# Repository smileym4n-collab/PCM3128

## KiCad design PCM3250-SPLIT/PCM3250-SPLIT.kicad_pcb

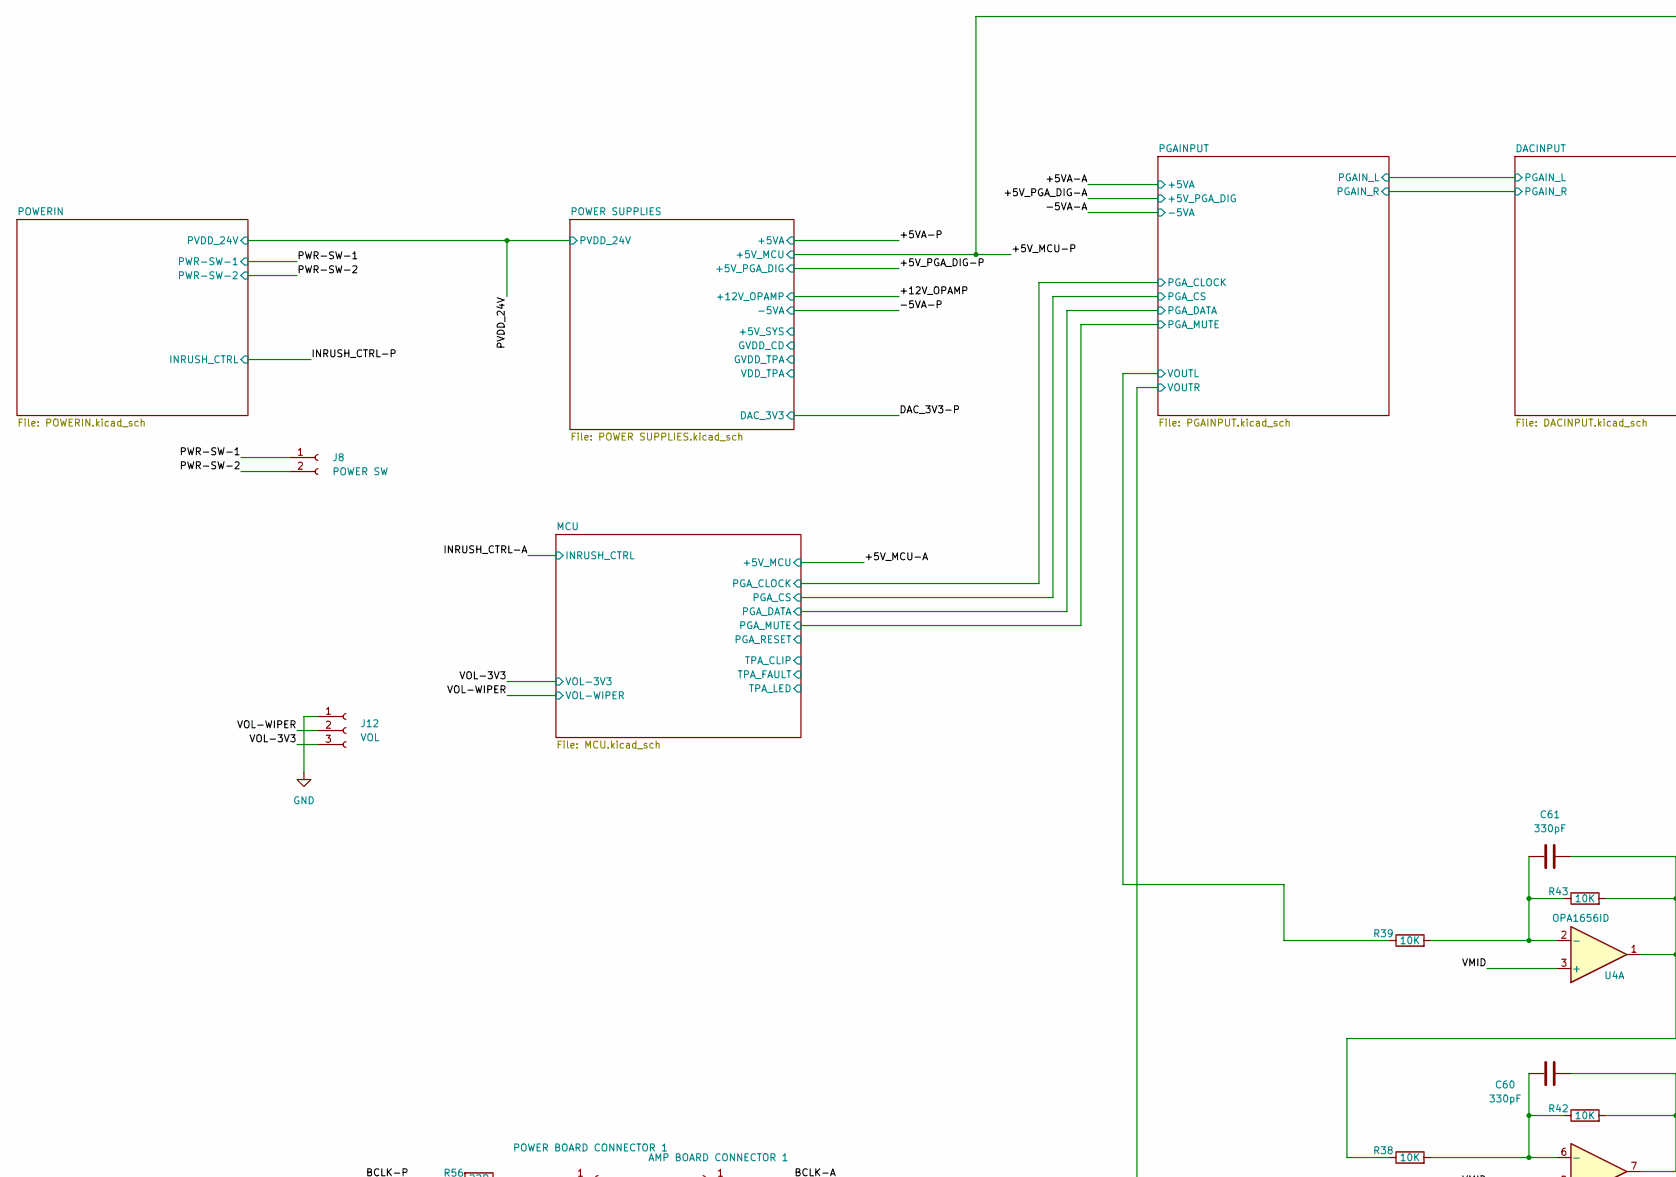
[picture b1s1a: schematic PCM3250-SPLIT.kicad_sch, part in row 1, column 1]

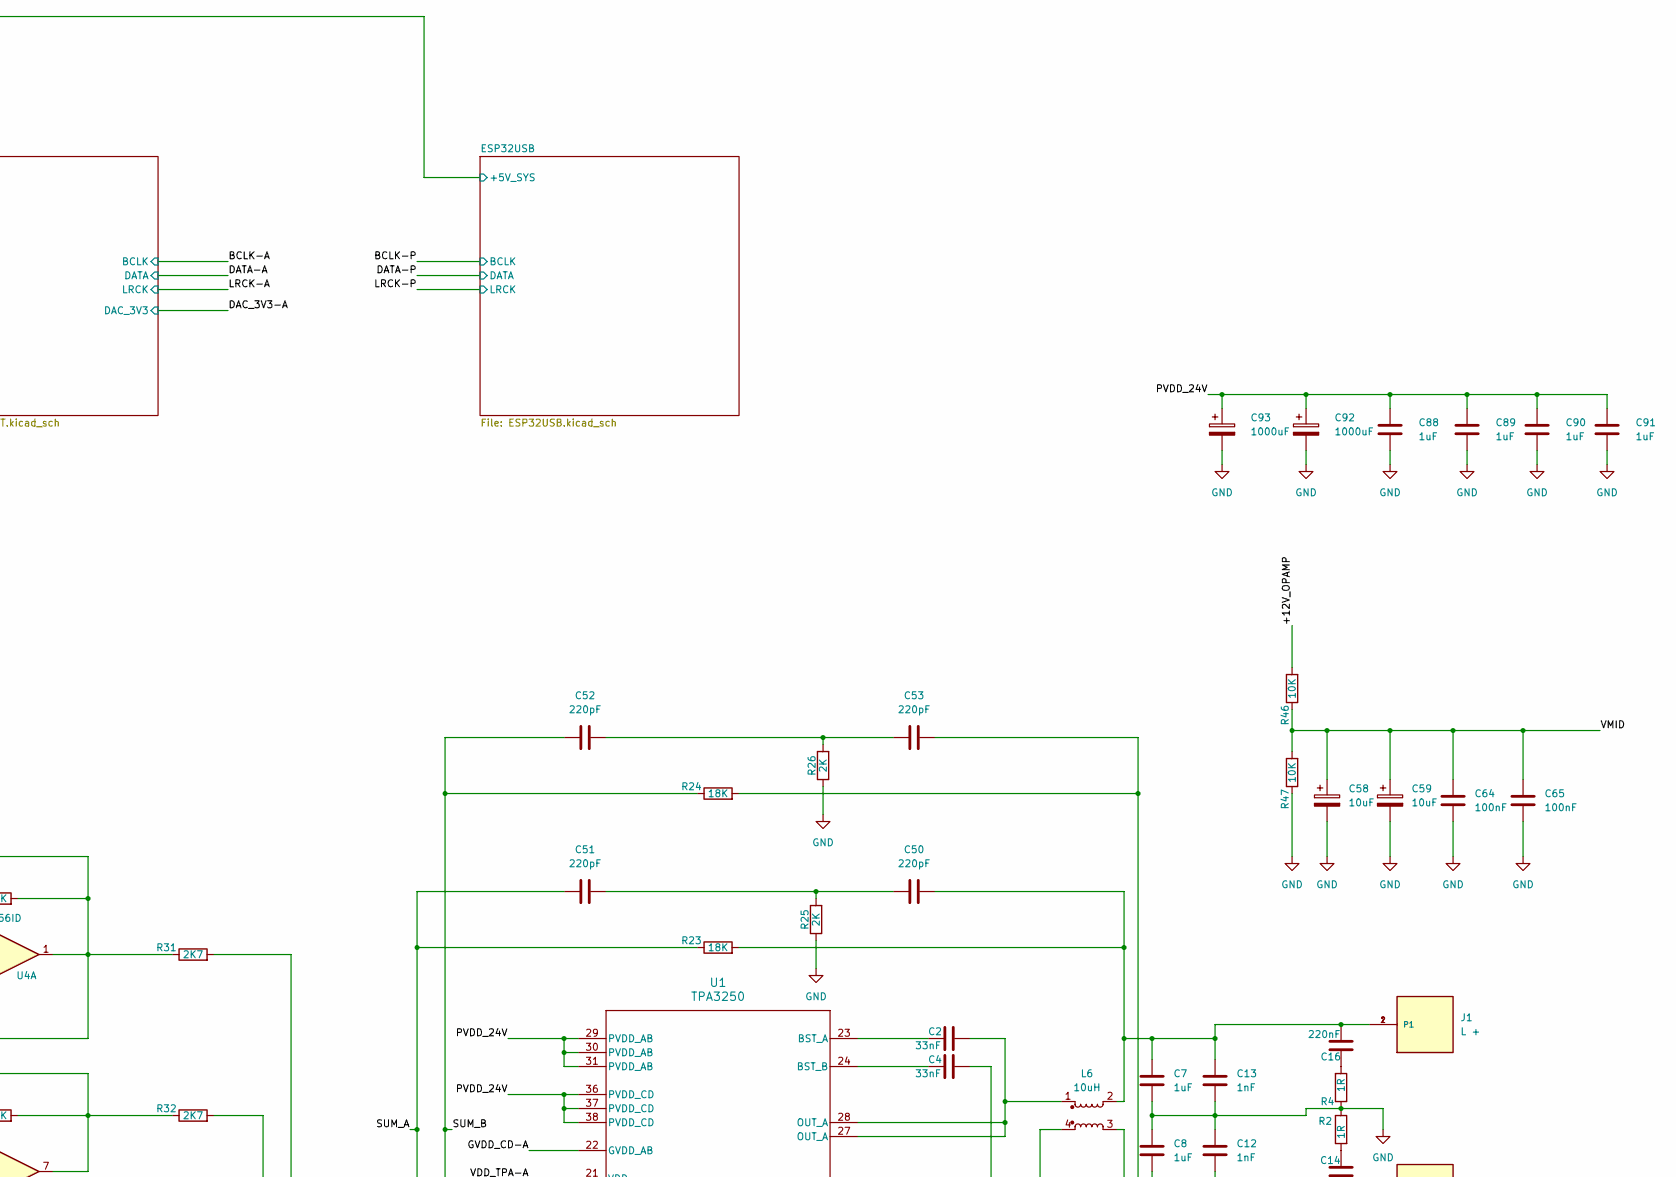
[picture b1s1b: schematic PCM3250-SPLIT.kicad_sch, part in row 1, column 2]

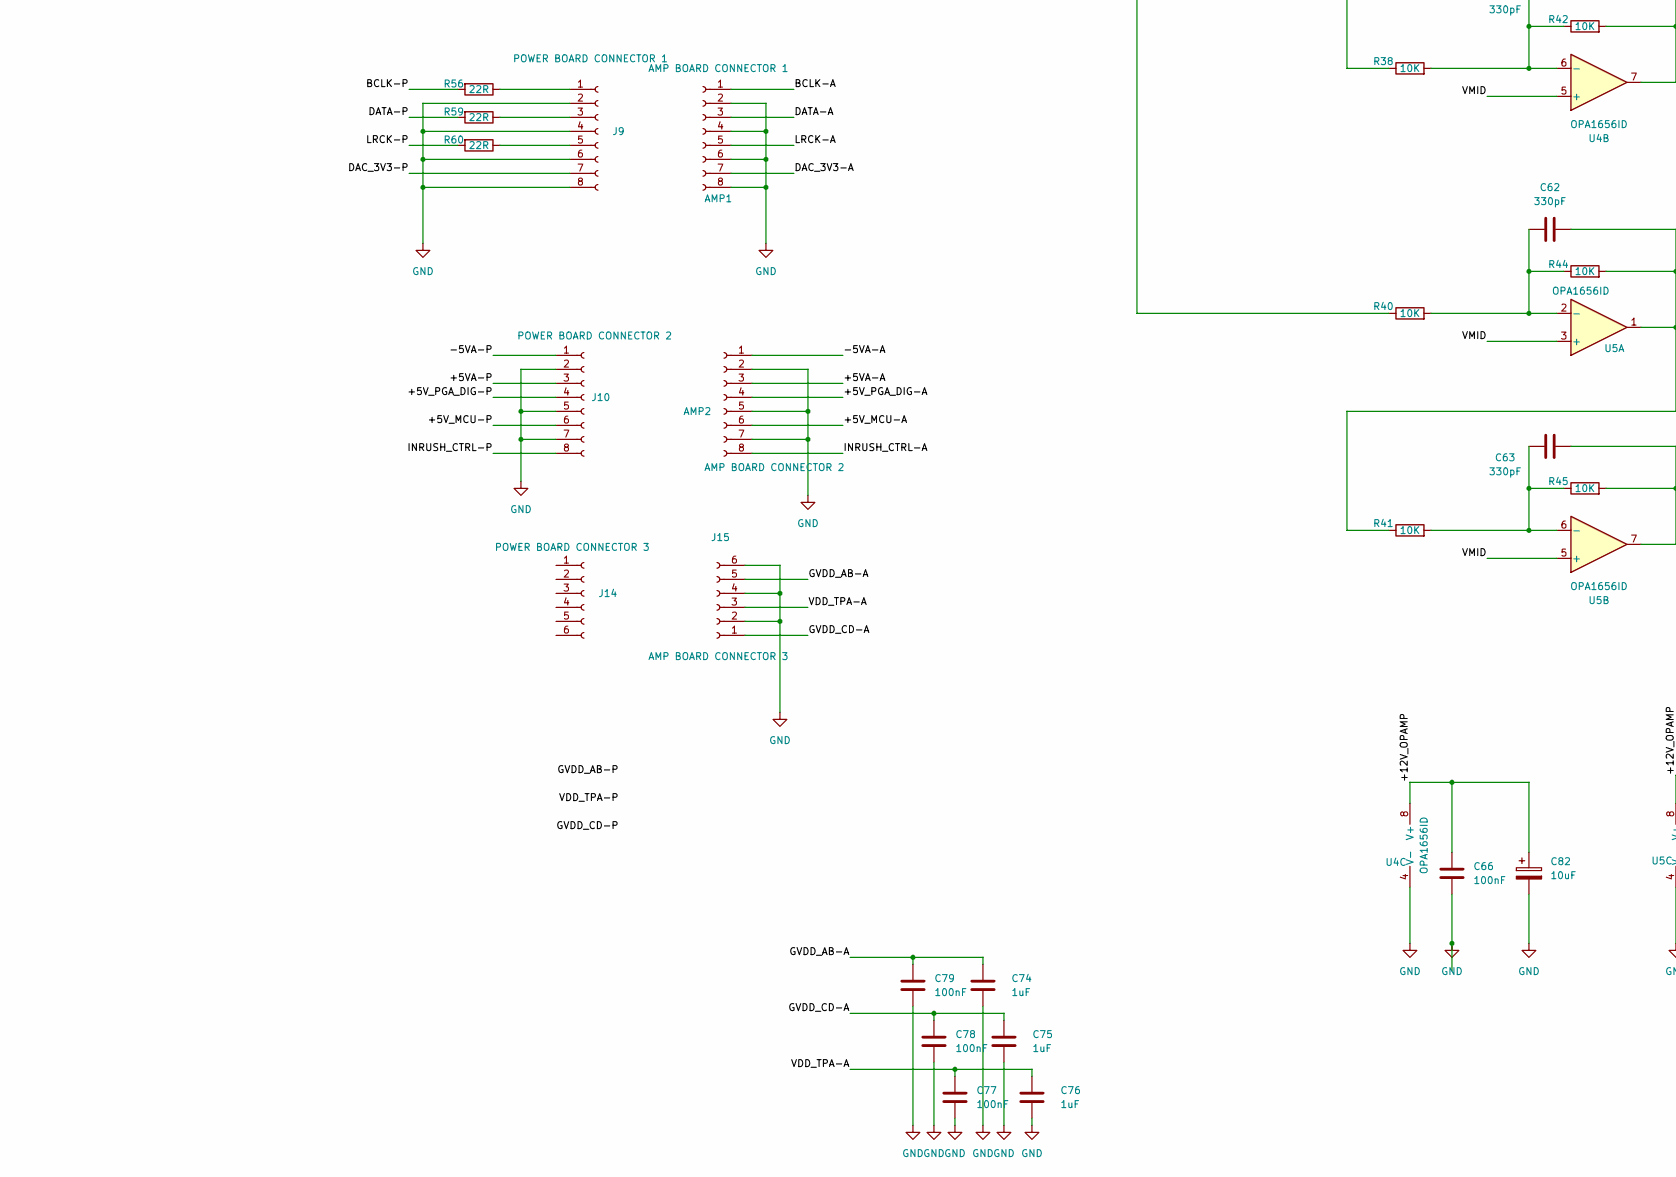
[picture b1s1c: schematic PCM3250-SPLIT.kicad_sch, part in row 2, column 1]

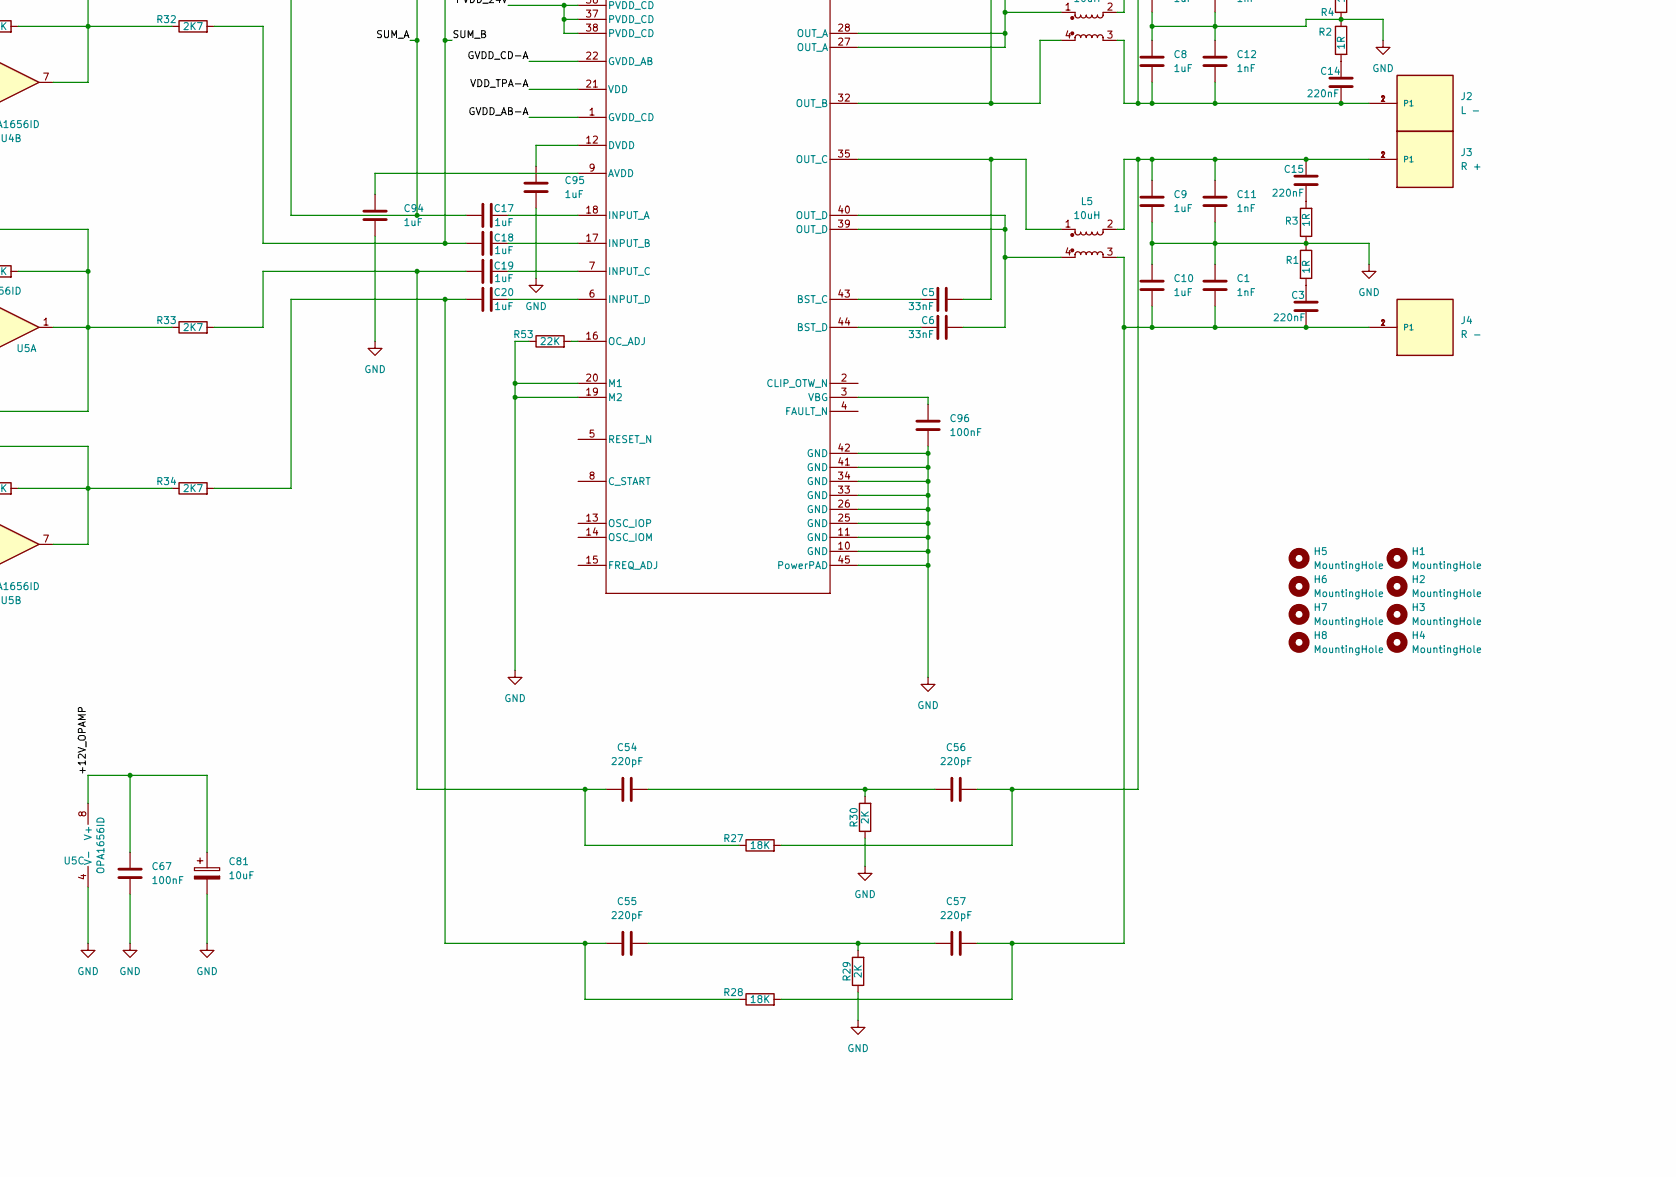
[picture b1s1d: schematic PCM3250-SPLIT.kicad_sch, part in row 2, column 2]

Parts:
AMP1: AMP BOARD CONNECTOR 1; JST_XH_B8B-XH-A_1x08_P2.50mm_Vertical
AMP2: AMP BOARD CONNECTOR 2; JST_XH_B8B-XH-A_1x08_P2.50mm_Vertical
C1, C11, C12, C13: 1nF; C_0805_2012Metric_Pad1.18x1.45mm_HandSolder
C2, C4, C5, C6: 33nF; C_0805_2012Metric_Pad1.18x1.45mm_HandSolder
C3, C14, C15, C16: 220nF; C_1206_3216Metric_Pad1.33x1.80mm_HandSolder
C7, C8, C9, C10: 1uF; C_Rect_L18.0mm_W8.0mm_P15.00mm_FKS3_FKP3
C17, C18, C19, C20: 1uF; C_Rect_L7.2mm_W5.5mm_P5.00mm_FKS2_FKP2_MKS2_MKP2
C50, C51, C52, C53, C54, C55, C56, C57: 220pF; C_0805_2012Metric_Pad1.18x1.45mm_HandSolder
C58, C59, C81, C82: 10uF; CP_Radial_D4.0mm_P2.00mm
C60, C61, C62, C63: 330pF; C_0805_2012Metric_Pad1.18x1.45mm_HandSolder
C64, C65, C66, C67, C77, C78, C79, C96: 100nF; C_1206_3216Metric_Pad1.33x1.80mm_HandSolder
C74, C75, C76, C88, C89, C90, C91, C94, C95: 1uF; C_1206_3216Metric_Pad1.33x1.80mm_HandSolder
C92, C93: 1000uF; CP_Radial_D12.5mm_P5.00mm
H1, H2, H3, H4, H5, H6, H7, H8: MountingHole; MountingHole_4.3mm_M4
J1: L +; TE_62409-1; PART_DESCRIPTION CONN QC TAB 0.250 SOLDER
J2: L -; TE_62409-1; PART_DESCRIPTION CONN QC TAB 0.250 SOLDER
J3: R +; TE_62409-1; PART_DESCRIPTION CONN QC TAB 0.250 SOLDER
J4: R -; TE_62409-1; PART_DESCRIPTION CONN QC TAB 0.250 SOLDER
J8: POWER SW; JST_XH_B2B-XH-A_1x02_P2.50mm_Vertical
J9: POWER BOARD CONNECTOR 1; JST_XH_B8B-XH-A_1x08_P2.50mm_Vertical
J10: POWER BOARD CONNECTOR 2; JST_XH_B8B-XH-A_1x08_P2.50mm_Vertical
J12: VOL; JST_XH_B3B-XH-A_1x03_P2.50mm_Vertical
J14: POWER BOARD CONNECTOR 3; JST_XH_B6B-XH-A_1x06_P2.50mm_Vertical
J15: AMP BOARD CONNECTOR 3; JST_XH_B6B-XH-A_1x06_P2.50mm_Vertical
L5, L6: 10uH; CSAD0660-100M
R1, R2, R3, R4: 1R; R_2512_6332Metric_Pad1.40x3.35mm_HandSolder
R23, R24, R27, R28: 18K; R_0805_2012Metric_Pad1.20x1.40mm_HandSolder
R25, R26, R29, R30: 2K; R_0805_2012Metric_Pad1.20x1.40mm_HandSolder
R31, R32, R33, R34: 2K7; R_0805_2012Metric_Pad1.20x1.40mm_HandSolder
R38, R39, R40, R41, R42, R43, R44, R45, R46, R47: 10K; R_0805_2012Metric_Pad1.20x1.40mm_HandSolder
R53: 22K; R_0805_2012Metric_Pad1.20x1.40mm_HandSolder
R56, R59, R60: 22R; R_0603_1608Metric_Pad0.98x0.95mm_HandSolder
U1: TPA3250
U4, U5: OPA1656ID; SOIC-8_3.9x4.9mm_P1.27mm

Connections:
/+5VA-A: AMP2.3; also elsewhere on the board
/+5VA-P: J10.3; also elsewhere on the board
/+5V_MCU-A: AMP2.6; also elsewhere on the board
/+5V_MCU-P: J10.6; also elsewhere on the board
/+5V_PGA_DIG-A: AMP2.4; also elsewhere on the board
/+5V_PGA_DIG-P: J10.4; also elsewhere on the board
/+12V_OPAMP: C66.1, C67.1, C81.1, C82.1, R46.2, U4.8 (V+), U5.8 (V+); also elsewhere on the board
/-5VA-A: AMP2.1; also elsewhere on the board
/-5VA-P: J10.1; also elsewhere on the board
/BCLK-A: AMP1.1; also elsewhere on the board
/BCLK-P: R56.2; also elsewhere on the board
/DAC_3V3-A: AMP1.7; also elsewhere on the board
/DATA-A: AMP1.3; also elsewhere on the board
/DATA-P: R59.2; also elsewhere on the board
/GVDD_AB-A: C74.1, C79.1, J15.5, U1.1 (GVDD_CD)
/GVDD_CD-A: C75.1, C78.1, J15.1, U1.22 (GVDD_AB)
/INRUSH_CTRL-A: AMP2.8; also elsewhere on the board
/INRUSH_CTRL-P: J10.8; also elsewhere on the board
/LRCK-A: AMP1.5; also elsewhere on the board
/LRCK-P: R60.2; also elsewhere on the board
/PGAINPUT/VOUTL: R39.1; also elsewhere on the board
/PGAINPUT/VOUTR: R40.1; also elsewhere on the board
/PVDD_24V: C88.1, C89.1, C90.1, C91.1, C92.1, C93.1, U1.29 (PVDD_AB), U1.30 (PVDD_AB), U1.31 (PVDD_AB), U1.36 (PVDD_CD), U1.37 (PVDD_CD), U1.38 (PVDD_CD); also elsewhere on the board
/PWR-SW-1: J8.1; also elsewhere on the board
/SUM_A: C17.1, C51.1, R23.1, R31.2
/SUM_B: C18.1, C52.1, R24.1, R32.2
/VDD_TPA-A: C76.1, C77.1, J15.3, U1.21 (VDD)
/VMID: C58.1, C59.1, C64.1, C65.1, R46.1, R47.2, U4.3 (+), U4.5 (+), U5.3 (+), U5.5 (+)
/VOL-3V3: J12.3; also elsewhere on the board
/VOL-WIPER: J12.2; also elsewhere on the board
GND: AMP1.2, AMP1.4, AMP1.6, AMP1.8, AMP2.2, AMP2.5, AMP2.7, C1.1, C7.1, C8.2, C9.1, C10.2, C11.2, C12.1, C13.2, C58.2, C59.2, C64.2, C65.2, C66.2, C67.2, C74.2, C75.2, C76.2, C77.2, C78.2, C79.2, C81.2, C82.2, C88.2, C89.2, C90.2, C91.2, C92.2, C93.2, C94.2, C95.2, C96.2, J8.2, J9.2, J9.4, J9.6, J9.8, J10.2, J10.5, J10.7, J12.1, J15.2, J15.4, J15.6, R1.1, R2.1, R3.1, R4.1, R25.1, R26.1, R29.1, R30.1, R47.1, R53.1, U1.10 (GND), U1.11 (GND), U1.19 (M2), U1.20 (M1), U1.25 (GND), U1.26 (GND), U1.33 (GND), U1.34 (GND), U1.41 (GND), U1.42 (GND), U1.45 (PowerPAD), U4.4 (V-), U5.4 (V-); also elsewhere on the board
unnamed: C1.2, C3.2, C10.1, C57.2, J4.1, J4.2 (P1), L5.3, R28.2
unnamed: C2.2, L6.1, U1.27 (OUT_A), U1.28 (OUT_A)
unnamed: C3.1, R1.2
unnamed: C6.2, L5.4, U1.39 (OUT_D), U1.40 (OUT_D)
unnamed: C9.2, C11.1, C15.2, C56.2, J3.1, J3.2 (P1), L5.2, R27.2
unnamed: C8.1, C12.2, C14.2, C53.2, J2.1, J2.2 (P1), L6.3, R24.2
unnamed: C7.2, C13.1, C16.2, C50.2, J1.1, J1.2 (P1), L6.2, R23.2
unnamed: C14.1, R2.2
unnamed: C15.1, R3.2
unnamed: C16.1, R4.2
unnamed: C19.1, C54.1, R27.1, R33.2
unnamed: C20.1, C55.1, R28.1, R34.2
unnamed: C50.1, C51.2, R25.2
unnamed: C52.2, C53.1, R26.2
unnamed: C54.2, C56.1, R30.2
unnamed: C55.2, C57.1, R29.2
unnamed: C60.2, R32.1, R42.2, U4.7
unnamed: C61.2, R31.1, R38.1, R43.2, U4.1
unnamed: C62.2, R33.1, R41.1, R44.2, U5.1
unnamed: C63.2, R34.1, R45.2, U5.7
unnamed: J9.1, R56.1
unnamed: J9.3, R59.1
unnamed: J9.5, R60.1
unnamed: C94.1, U1.9 (AVDD)
unnamed: C2.1, U1.23 (BST_A)
unnamed: C4.1, U1.24 (BST_B)
unnamed: C5.1, U1.43 (BST_C)
unnamed: C6.1, U1.44 (BST_D)
unnamed: C95.1, U1.12 (DVDD)
unnamed: C17.2, U1.18 (INPUT_A)
unnamed: C18.2, U1.17 (INPUT_B)
unnamed: C19.2, U1.7 (INPUT_C)
unnamed: C20.2, U1.6 (INPUT_D)
unnamed: R53.2, U1.16 (OC_ADJ)
unnamed: C4.2, L6.4, U1.32 (OUT_B)
unnamed: C5.2, L5.1, U1.35 (OUT_C)
unnamed: C96.1, U1.3 (VBG)
unnamed: C61.1, R39.2, R43.1, U4.2 (-)
unnamed: C60.1, R38.2, R42.1, U4.6 (-)
unnamed: C62.1, R40.2, R44.1, U5.2 (-)
unnamed: C63.1, R41.2, R45.1, U5.6 (-)

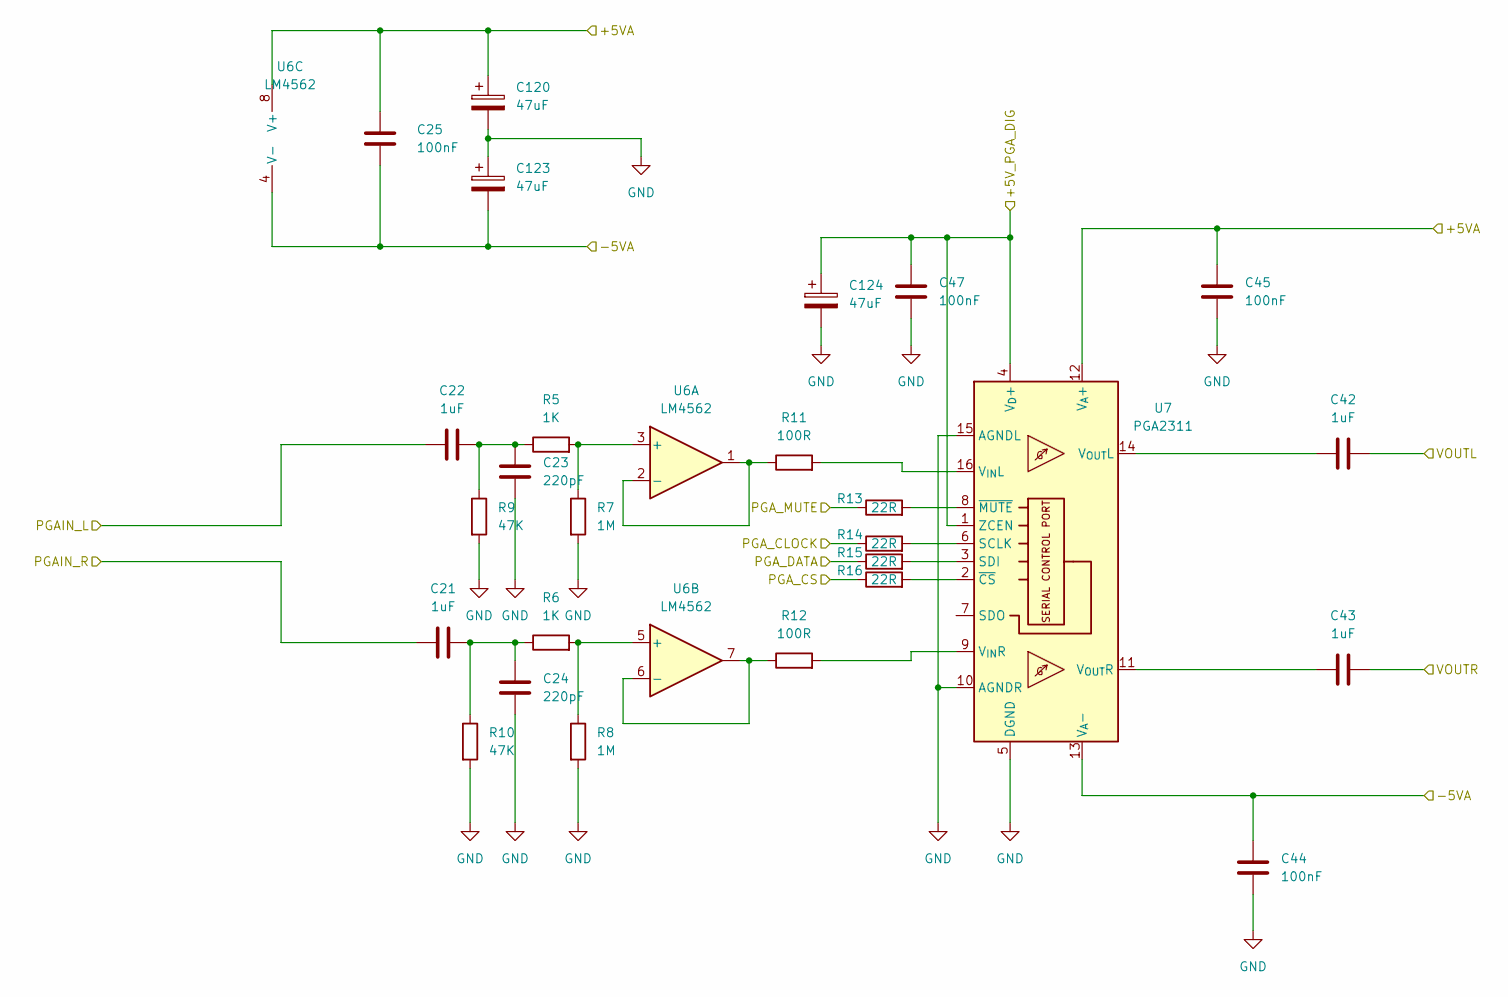
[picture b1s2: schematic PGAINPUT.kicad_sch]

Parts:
C21, C22, C42, C43: 1uF; C_Rect_L7.2mm_W5.5mm_P5.00mm_FKS2_FKP2_MKS2_MKP2
C23, C24: 220pF; C_0805_2012Metric_Pad1.18x1.45mm_HandSolder
C25, C44, C45, C47: 100nF; C_1206_3216Metric_Pad1.33x1.80mm_HandSolder
C120, C123, C124: 47uF; CP_Radial_D5.0mm_P2.50mm
R5, R6: 1K; R_0805_2012Metric_Pad1.20x1.40mm_HandSolder
R7, R8: 1M; R_0805_2012Metric_Pad1.20x1.40mm_HandSolder
R9, R10: 47K; R_0805_2012Metric_Pad1.20x1.40mm_HandSolder
R11, R12: 100R; R_0805_2012Metric_Pad1.20x1.40mm_HandSolder
R13, R14, R15, R16: 22R; R_0805_2012Metric_Pad1.20x1.40mm_HandSolder
U6: LM4562; DIP-8_W7.62mm_Socket
U7: PGA2311; DIP-16_W7.62mm_Socket

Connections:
/+5VA-A: C25.1, C45.1, C120.1, U6.8 (V+), U7.12 (V_{A}+); also elsewhere on the board
/+5V_PGA_DIG-A: C47.1, C124.1, U7.1 (ZCEN), U7.4 (V_{D}+); also elsewhere on the board
/-5VA-A: C25.2, C44.1, C123.2, U6.4 (V-), U7.13 (V_{A}-); also elsewhere on the board
/DACINPUT/PGAIN_L: C22.1; also elsewhere on the board
/DACINPUT/PGAIN_R: C21.1; also elsewhere on the board
/MCU/PGA_CLOCK: R14.1; also elsewhere on the board
/MCU/PGA_CS: R16.1; also elsewhere on the board
/MCU/PGA_DATA: R15.1; also elsewhere on the board
/MCU/PGA_MUTE: R13.1; also elsewhere on the board
/PGAINPUT/VOUTL: C42.2; also elsewhere on the board
/PGAINPUT/VOUTR: C43.2; also elsewhere on the board
GND: C23.2, C24.2, C44.2, C45.2, C47.2, C120.2, C123.1, C124.2, R7.2, R8.2, R9.2, R10.2, U7.5 (DGND), U7.10 (AGNDR), U7.15 (AGNDL); also elsewhere on the board
unnamed: C21.2, C24.1, R6.1, R10.1
unnamed: C22.2, C23.1, R5.1, R9.1
unnamed: R5.2, R7.1, U6.3 (+)
unnamed: R11.1, U6.1, U6.2 (-)
unnamed: R6.2, R8.1, U6.5 (+)
unnamed: R12.1, U6.6 (-), U6.7
unnamed: R14.2, U7.6 (SCLK)
unnamed: R15.2, U7.3 (SDI)
unnamed: R11.2, U7.16 (V_{IN}L)
unnamed: R12.2, U7.9 (V_{IN}R)
unnamed: C42.1, U7.14 (V_{OUT}L)
unnamed: C43.1, U7.11 (V_{OUT}R)
unnamed: R16.2, U7.2 (~CS)
unnamed: R13.2, U7.8 (~MUTE)

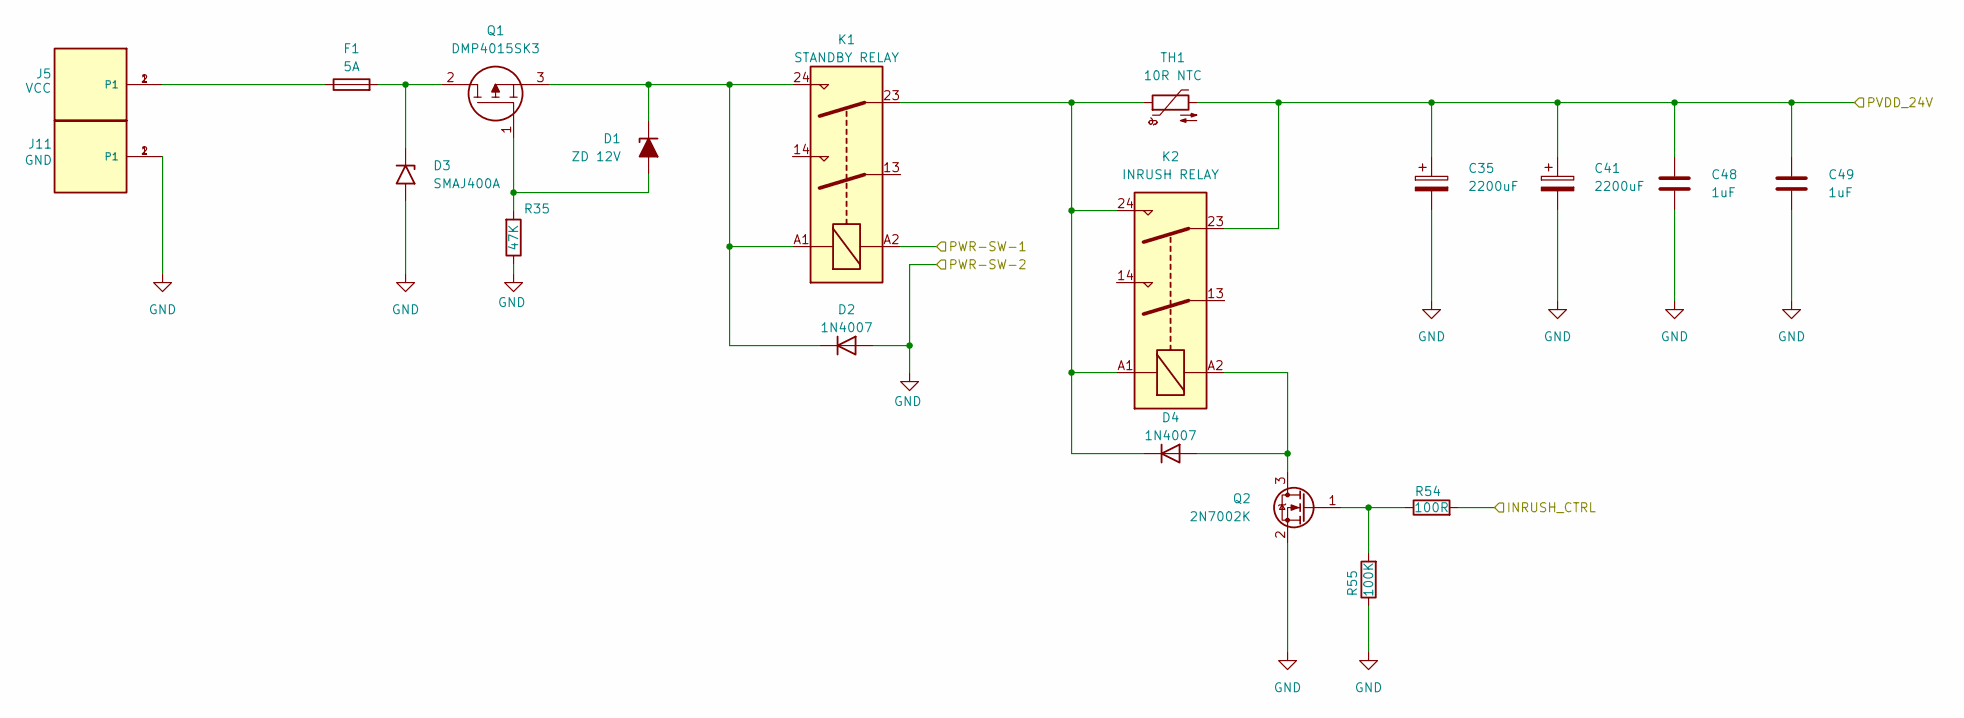
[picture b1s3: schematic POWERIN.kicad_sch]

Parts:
C35, C41: 2200uF; CP_Radial_D16.0mm_P7.50mm
C48, C49: 1uF; C_1206_3216Metric_Pad1.33x1.80mm_HandSolder
D1: ZD 12V; D_DO-201AD_P12.70mm_Horizontal
D2, D4: 1N4007; D_DO-41_SOD81_P10.16mm_Horizontal
D3: SMAJ400A; D_SMA
F1: 5A; Fuseholder_Cylinder-5x20mm_Stelvio-Kontek_PTF78_Horizontal_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
J5: VCC; TE_62409-1; PART_DESCRIPTION CONN QC TAB 0.250 SOLDER
J11: GND; TE_62409-1; PART_DESCRIPTION CONN QC TAB 0.250 SOLDER
K1: STANDBY RELAY; Relay_DPST_Omron_G2RL-2A
K2: INRUSH RELAY; Relay_DPST_Omron_G2RL-2A
Q1: DMP4015SK3; DMP4015SK313; Manufacturer_Part_Number DMP4015SK3-13
Q2: 2N7002K; SOT-23
R35: 47K; R_0805_2012Metric_Pad1.20x1.40mm_HandSolder
R54: 100R; R_0805_2012Metric_Pad1.20x1.40mm_HandSolder
R55: 100K; R_0805_2012Metric_Pad1.20x1.40mm_HandSolder
TH1: 10R NTC; C_Disc_D16.0mm_W5.0mm_P7.50mm

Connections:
/INRUSH_CTRL-P: R54.2; also elsewhere on the board
/PVDD_24V: C35.1, C41.1, C48.1, C49.1, K2.23, TH1.2; also elsewhere on the board
/PWR-SW-1: K1.A2; also elsewhere on the board
GND: C35.2, C41.2, C48.2, C49.2, D2.2 (A), D3.2 (A2), J11.1, J11.2 (P1), Q2.2 (S), R35.1, R55.1; also elsewhere on the board
unnamed: D1.2 (A), Q1.1, R35.2
unnamed: D1.1 (K), D2.1 (K), K1.24, K1.A1, Q1.3
unnamed: D3.1 (A1), F1.2, Q1.2
unnamed: D4.2 (A), K2.A2, Q2.3 (D)
unnamed: D4.1 (K), K1.23, K2.24, K2.A1, TH1.1
unnamed: F1.1, J5.1, J5.2 (P1)
unnamed: Q2.1 (G), R54.1, R55.2

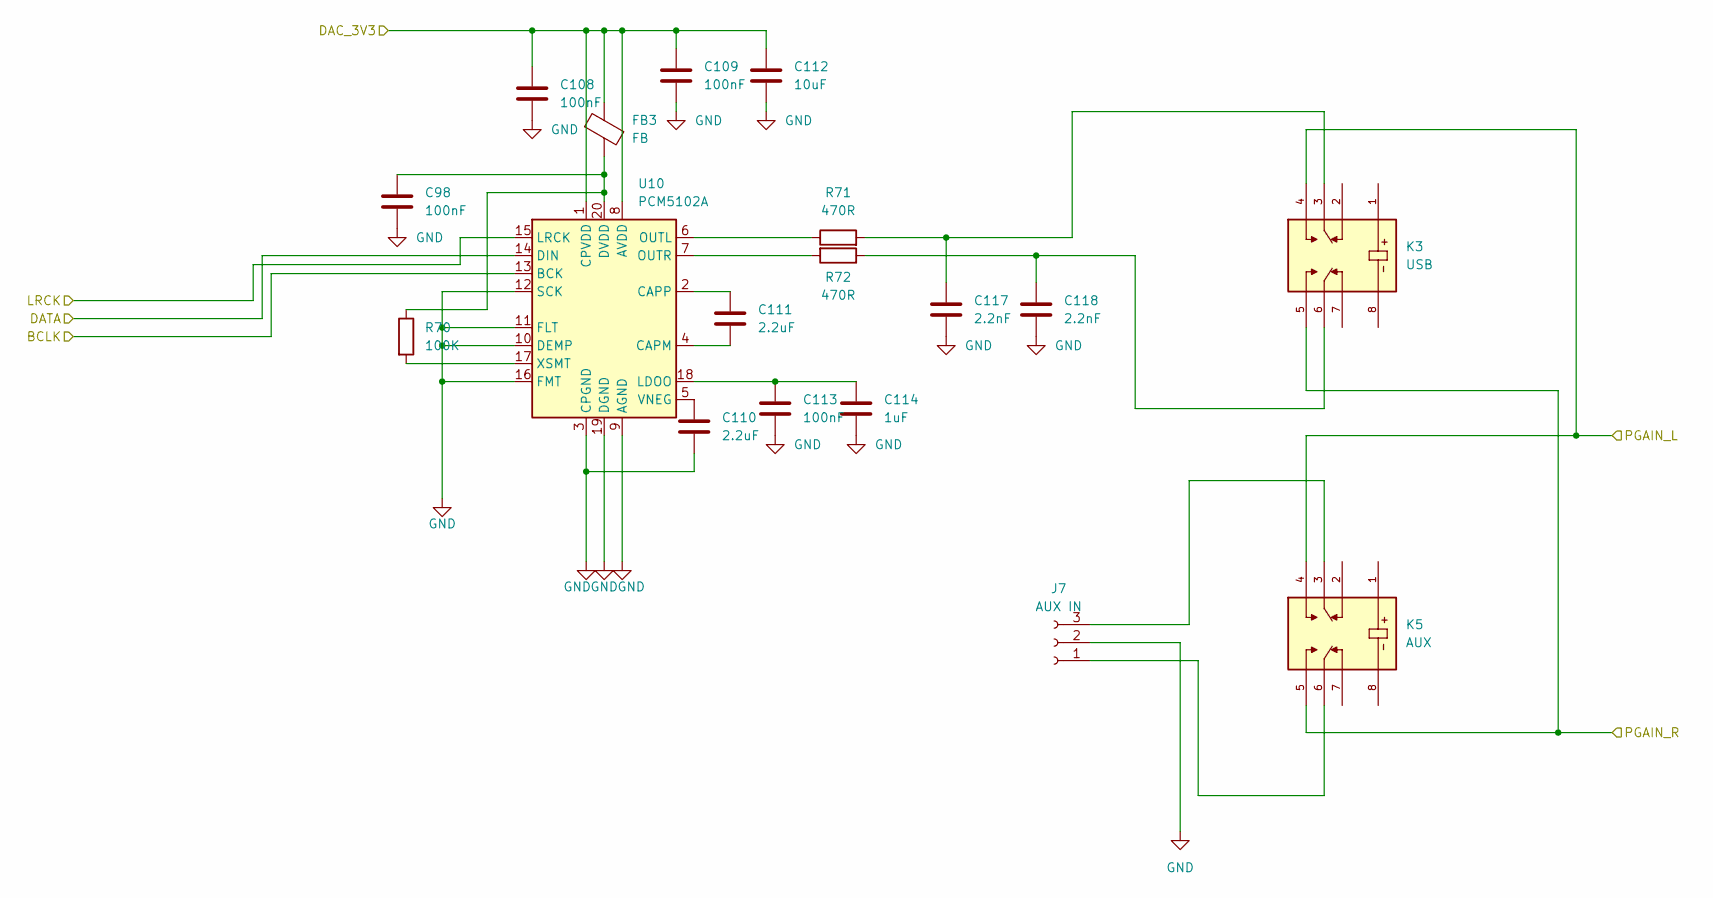
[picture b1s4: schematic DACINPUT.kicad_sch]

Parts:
C98, C108, C109, C113: 100nF; C_1206_3216Metric_Pad1.33x1.80mm_HandSolder
C110, C111: 2.2uF; C_0805_2012Metric_Pad1.18x1.45mm_HandSolder
C112: 10uF; C_0805_2012Metric_Pad1.18x1.45mm_HandSolder
C114: 1uF; C_1206_3216Metric_Pad1.33x1.80mm_HandSolder
C117, C118: 2.2nF; C_0805_2012Metric_Pad1.18x1.45mm_HandSolder
FB3: FB; L_1206_3216Metric_Pad1.42x1.75mm_HandSolder
J7: AUX IN; JST_XH_B3B-XH-A_1x03_P2.50mm_Vertical
K3: USB; RELAY_G6K-2P-Y_DC3; PARTREV K106-E1-11
K5: AUX; RELAY_G6K-2P-Y_DC3; PARTREV K106-E1-11
R70: 100K; R_0805_2012Metric_Pad1.20x1.40mm_HandSolder
R71, R72: 470R; R_0805_2012Metric_Pad1.20x1.40mm_HandSolder
U10: PCM5102A; TSSOP-20_4.4x6.5mm_P0.65mm

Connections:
/BCLK-A: U10.13 (BCK); also elsewhere on the board
/DACINPUT/PGAIN_L: K3.4, K5.4; also elsewhere on the board
/DACINPUT/PGAIN_R: K3.5, K5.5; also elsewhere on the board
/DAC_3V3-A: C108.1, C109.1, C112.1, FB3.1, U10.1 (CPVDD), U10.8 (AVDD); also elsewhere on the board
/DATA-A: U10.14 (DIN); also elsewhere on the board
/LRCK-A: U10.15 (LRCK); also elsewhere on the board
GND: C98.2, C108.2, C109.2, C110.2, C112.2, C113.2, C114.2, C117.2, C118.2, J7.2, U10.3 (CPGND), U10.9 (AGND), U10.10 (DEMP), U10.11 (FLT), U10.12 (SCK), U10.16 (FMT), U10.19 (DGND); also elsewhere on the board
unnamed: C117.1, K3.3, R71.2
unnamed: C118.1, K3.6, R72.1
unnamed: J7.1, K5.6
unnamed: J7.3, K5.3
unnamed: C111.2, U10.4 (CAPM)
unnamed: C111.1, U10.2 (CAPP)
unnamed: C98.1, FB3.2, R70.1, U10.20 (DVDD)
unnamed: C113.1, C114.1, U10.18 (LDOO)
unnamed: R71.1, U10.6 (OUTL)
unnamed: R72.2, U10.7 (OUTR)
unnamed: C110.1, U10.5 (VNEG)
unnamed: R70.2, U10.17 (XSMT)
